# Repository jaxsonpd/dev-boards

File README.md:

# dev-boards
A collection of development boards developed by me

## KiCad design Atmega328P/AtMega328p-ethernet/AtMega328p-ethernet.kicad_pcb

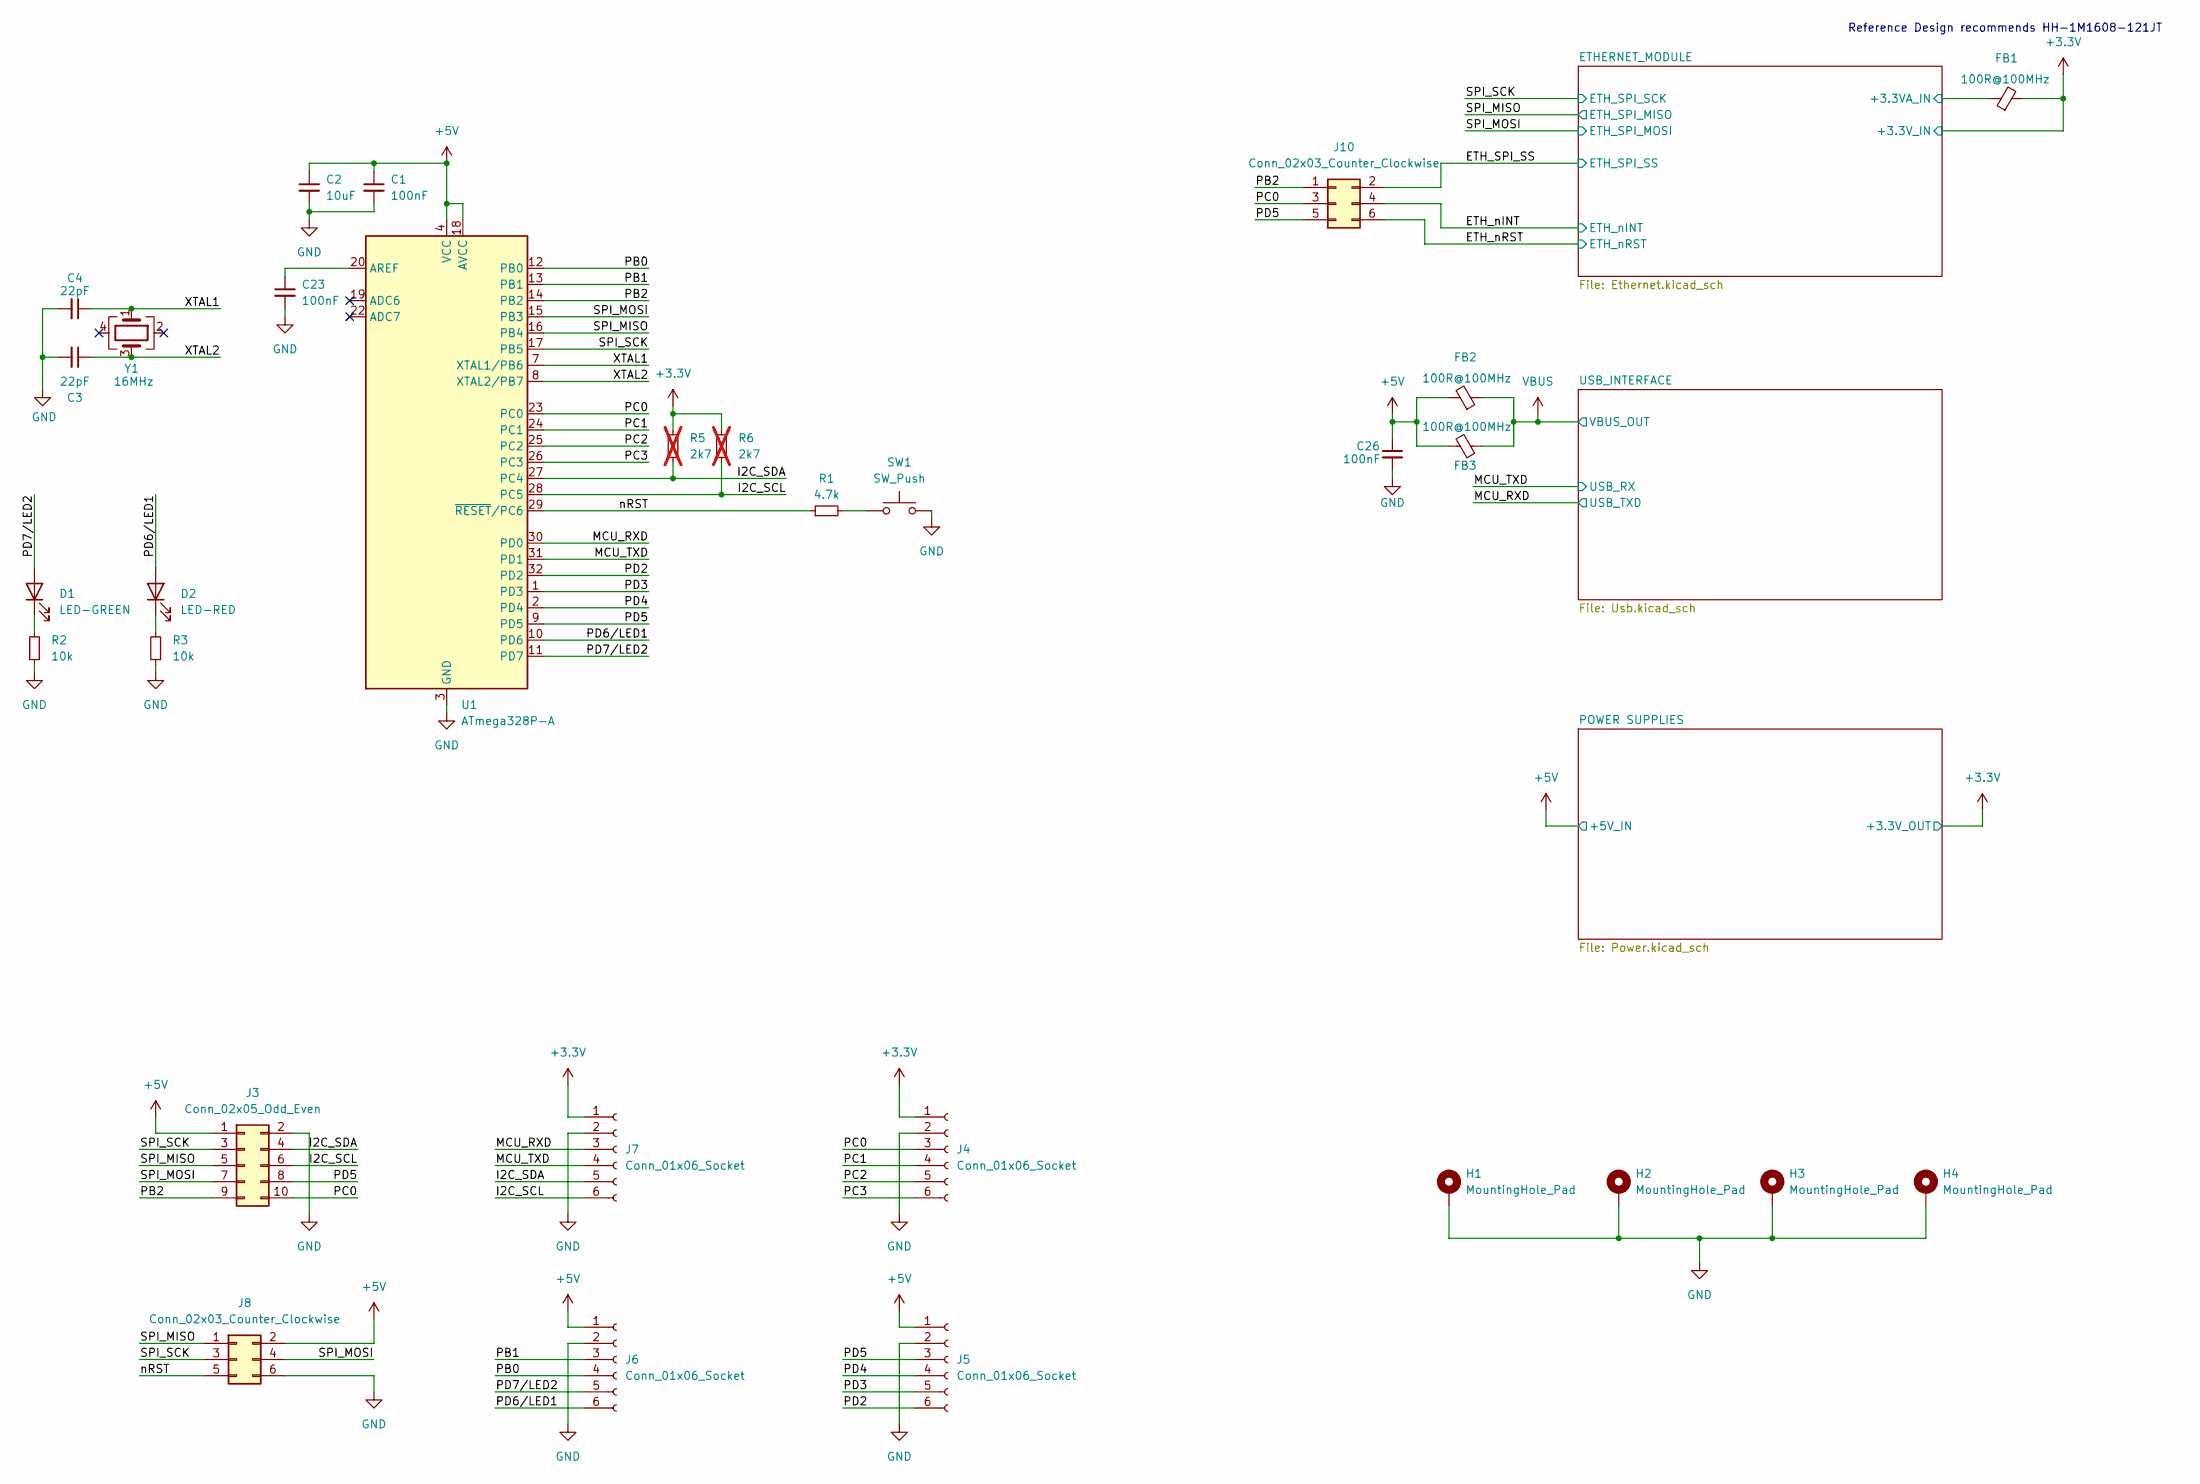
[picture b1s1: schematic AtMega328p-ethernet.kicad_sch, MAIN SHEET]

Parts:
C1, C23, C26: 100nF; C_0603_1608Metric; LCSC C14663
C2: 10uF; C_1206_3216Metric; LCSC C13585
C3, C4: 22pF; C_0603_1608Metric; LCSC C1653
D1: LED-GREEN; LED_0805_2012Metric; LCSC C2297
D2: LED-RED; LED_0805_2012Metric; LCSC C2296
FB1, FB2, FB3: 100R@100MHz; L_0603_1608Metric; LCSC C1015
H1, H2, H3, H4: MountingHole_Pad; MountingHole_3.2mm_M3_DIN965_Pad
J3: Conn_02x05_Odd_Even; IDC-Header_2x05_P2.54mm_Horizontal
J4, J5, J6, J7: Conn_01x06_Socket; PinHeader_1x06_P2.54mm_Vertical
J8, J10: Conn_02x03_Counter_Clockwise; PinHeader_2x03_P2.54mm_Vertical
R1: 4.7k; R_0603_1608Metric; LCSC C23162
R2, R3: 10k; R_0603_1608Metric; LCSC C25804
R5: 2k7; R_0603_1608Metric; LCSC C13167; not fitted
R6: 2k7; R_0603_1608Metric; not fitted
SW1: SW_Push; SW_Push_1P1T_XKB_TS-1187A; LCSC C318884
U1: ATmega328P-A; TQFP-32_7x7mm_P0.8mm; LCSC C14877
Y1: 16MHz; Crystal_SMD_3225-4Pin_3.2x2.5mm; LCSC C13738

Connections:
+3.3V: FB1.2, J4.1, J7.1, R5.2, R6.2; also elsewhere on the board
+5V: C1.1, C2.1, C26.1, FB2.2, FB3.2, J3.1, J5.1, J6.1, J8.2, U1.4 (VCC), U1.6 (VCC), U1.18 (AVCC); also elsewhere on the board
/ETHERNET_MODULE/+3.3VA_IN: FB1.1; also elsewhere on the board
/ETH_SPI_SS: J10.2; also elsewhere on the board
/ETH_nINT: J10.4; also elsewhere on the board
/ETH_nRST: J10.6; also elsewhere on the board
/I2C_SCL: J3.6, J7.6, R6.1, U1.28 (PC5)
/I2C_SDA: J3.4, J7.5, R5.1, U1.27 (PC4)
/MCU_RXD: J7.3, U1.30 (PD0); also elsewhere on the board
/MCU_TXD: J7.4, U1.31 (PD1); also elsewhere on the board
/PB0: J6.4, U1.12 (PB0)
/PB1: J6.3, U1.13 (PB1)
/PB2: J3.9, J10.1, U1.14 (PB2)
/PC0: J3.10, J4.3, J10.3, U1.23 (PC0)
/PC1: J4.4, U1.24 (PC1)
/PC2: J4.5, U1.25 (PC2)
/PC3: J4.6, U1.26 (PC3)
/PD2: J5.6, U1.32 (PD2)
/PD3: J5.5, U1.1 (PD3)
/PD4: J5.4, U1.2 (PD4)
/PD5: J3.8, J5.3, J10.5, U1.9 (PD5)
/PD6/LED1: D2.2 (A), J6.6, U1.10 (PD6)
/PD7/LED2: D1.2 (A), J6.5, U1.11 (PD7)
/SPI_MISO: J3.5, J8.1, U1.16 (PB4); also elsewhere on the board
/SPI_MOSI: J3.7, J8.4, U1.15 (PB3); also elsewhere on the board
/SPI_SCK: J3.3, J8.3, U1.17 (PB5); also elsewhere on the board
/XTAL1: C4.1, U1.7 (XTAL1/PB6), Y1.1
/XTAL2: C3.1, U1.8 (XTAL2/PB7), Y1.3
/nRST: J8.5, R1.1, U1.29 (~RESET/PC6)
GND: C1.2, C2.2, C3.2, C4.2, C23.2, C26.2, H1.1, H2.1, H3.1, H4.1, J3.2, J4.2, J5.2, J6.2, J7.2, J8.6, R2.1, R3.1, SW1.2, U1.3 (GND), U1.5 (GND), U1.21 (GND); also elsewhere on the board
unnamed: D1.1 (K), R2.2
unnamed: D2.1 (K), R3.2
unnamed: R1.2, SW1.1
unnamed: C23.1, U1.20 (AREF)
VBUS: FB2.1, FB3.1; also elsewhere on the board

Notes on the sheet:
Reference Design recommends HH-1M1608-121JT

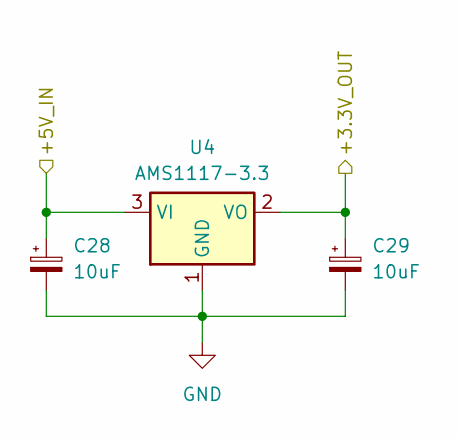
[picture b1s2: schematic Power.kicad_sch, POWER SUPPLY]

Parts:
C28, C29: 10uF; C_1206_3216Metric; LCSC C13585
U4: AMS1117-3.3; SOT-223-3_TabPin2; LCSC C6186

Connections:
+3.3V: C29.1, U4.2 (VO); also elsewhere on the board
+5V: C28.1, U4.3 (VI); also elsewhere on the board
GND: C28.2, C29.2, U4.1 (GND); also elsewhere on the board

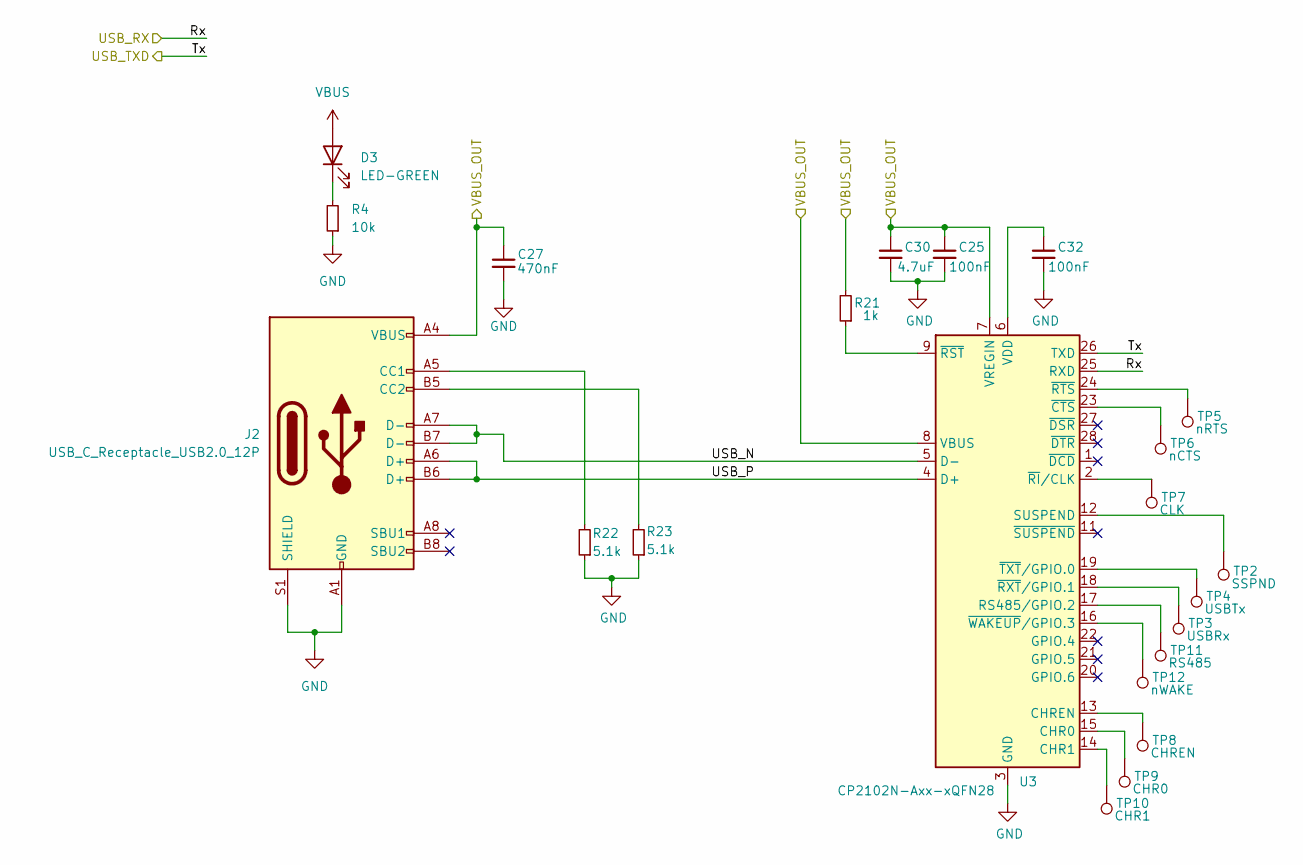
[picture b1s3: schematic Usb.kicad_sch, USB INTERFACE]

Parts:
C25, C32: 100nF; C_0603_1608Metric; LCSC C1647
C27: 470nF; C_0603_1608Metric; LCSC C1623
C30: 4.7uF; C_0603_1608Metric; LCSC C1647
D3: LED-GREEN; LED_0805_2012Metric; LCSC C2297
J2: USB_C_Receptacle_USB2.0_12P; USB_C_Receptacle_G-Switch_GT-USB-7010ASV; LCSC C2988369
R4: 10k; R_0603_1608Metric; LCSC C25804
R21: 1k; R_0603_1608Metric; LCSC C21190
R22, R23: 5.1k; R_0603_1608Metric; LCSC C23186
TP2: SSPND; TestPoint_Pad_1.0x1.0mm
TP3: USBRx; TestPoint_Pad_1.0x1.0mm
TP4: USBTx; TestPoint_Pad_1.0x1.0mm
TP5: nRTS; TestPoint_Pad_1.0x1.0mm
TP6: nCTS; TestPoint_Pad_1.0x1.0mm
TP7: CLK; TestPoint_Pad_1.0x1.0mm
TP8: CHREN; TestPoint_Pad_1.0x1.0mm
TP9: CHR0; TestPoint_Pad_1.0x1.0mm
TP10: CHR1; TestPoint_Pad_1.0x1.0mm
TP11: RS485; TestPoint_Pad_1.0x1.0mm
TP12: nWAKE; TestPoint_Pad_1.0x1.0mm
U3: CP2102N-Axx-xQFN28; QFN-28-1EP_5x5mm_P0.5mm_EP3.35x3.35mm; LCSC C6568

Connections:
/MCU_RXD: U3.26 (TXD); also elsewhere on the board
/MCU_TXD: U3.25 (RXD); also elsewhere on the board
/USB_INTERFACE/USB_N: J2.A7 (D-), J2.B7 (D-), U3.5 (D-)
/USB_INTERFACE/USB_P: J2.A6 (D+), J2.B6 (D+), U3.4 (D+)
GND: C25.2, C27.2, C30.2, C32.2, J2.A1 (GND), J2.A12 (GND), J2.B1 (GND), J2.B12 (GND), J2.S1 (SHIELD), R4.1, R22.1, R23.1, U3.3 (GND), U3.29 (GND); also elsewhere on the board
unnamed: D3.1 (K), R4.2
unnamed: J2.A5 (CC1), R22.2
unnamed: J2.B5 (CC2), R23.2
unnamed: TP9.1, U3.15 (CHR0)
unnamed: TP10.1, U3.14 (CHR1)
unnamed: TP8.1, U3.13 (CHREN)
unnamed: TP11.1, U3.17 (RS485/GPIO.2)
unnamed: TP2.1, U3.12 (SUSPEND)
unnamed: C32.1, U3.6 (VDD)
unnamed: TP6.1, U3.23 (~CTS)
unnamed: TP7.1, U3.2 (~RI/CLK)
unnamed: R21.1, U3.9 (~RST)
unnamed: TP5.1, U3.24 (~RTS)
unnamed: TP3.1, U3.18 (~RXT/GPIO.1)
unnamed: TP4.1, U3.19 (~TXT/GPIO.0)
unnamed: TP12.1, U3.16 (~WAKEUP/GPIO.3)
VBUS: C25.1, C27.1, C30.1, D3.2 (A), J2.A4 (VBUS), J2.A9 (VBUS), J2.B4 (VBUS), J2.B9 (VBUS), R21.2, U3.7 (VREGIN), U3.8 (VBUS); also elsewhere on the board

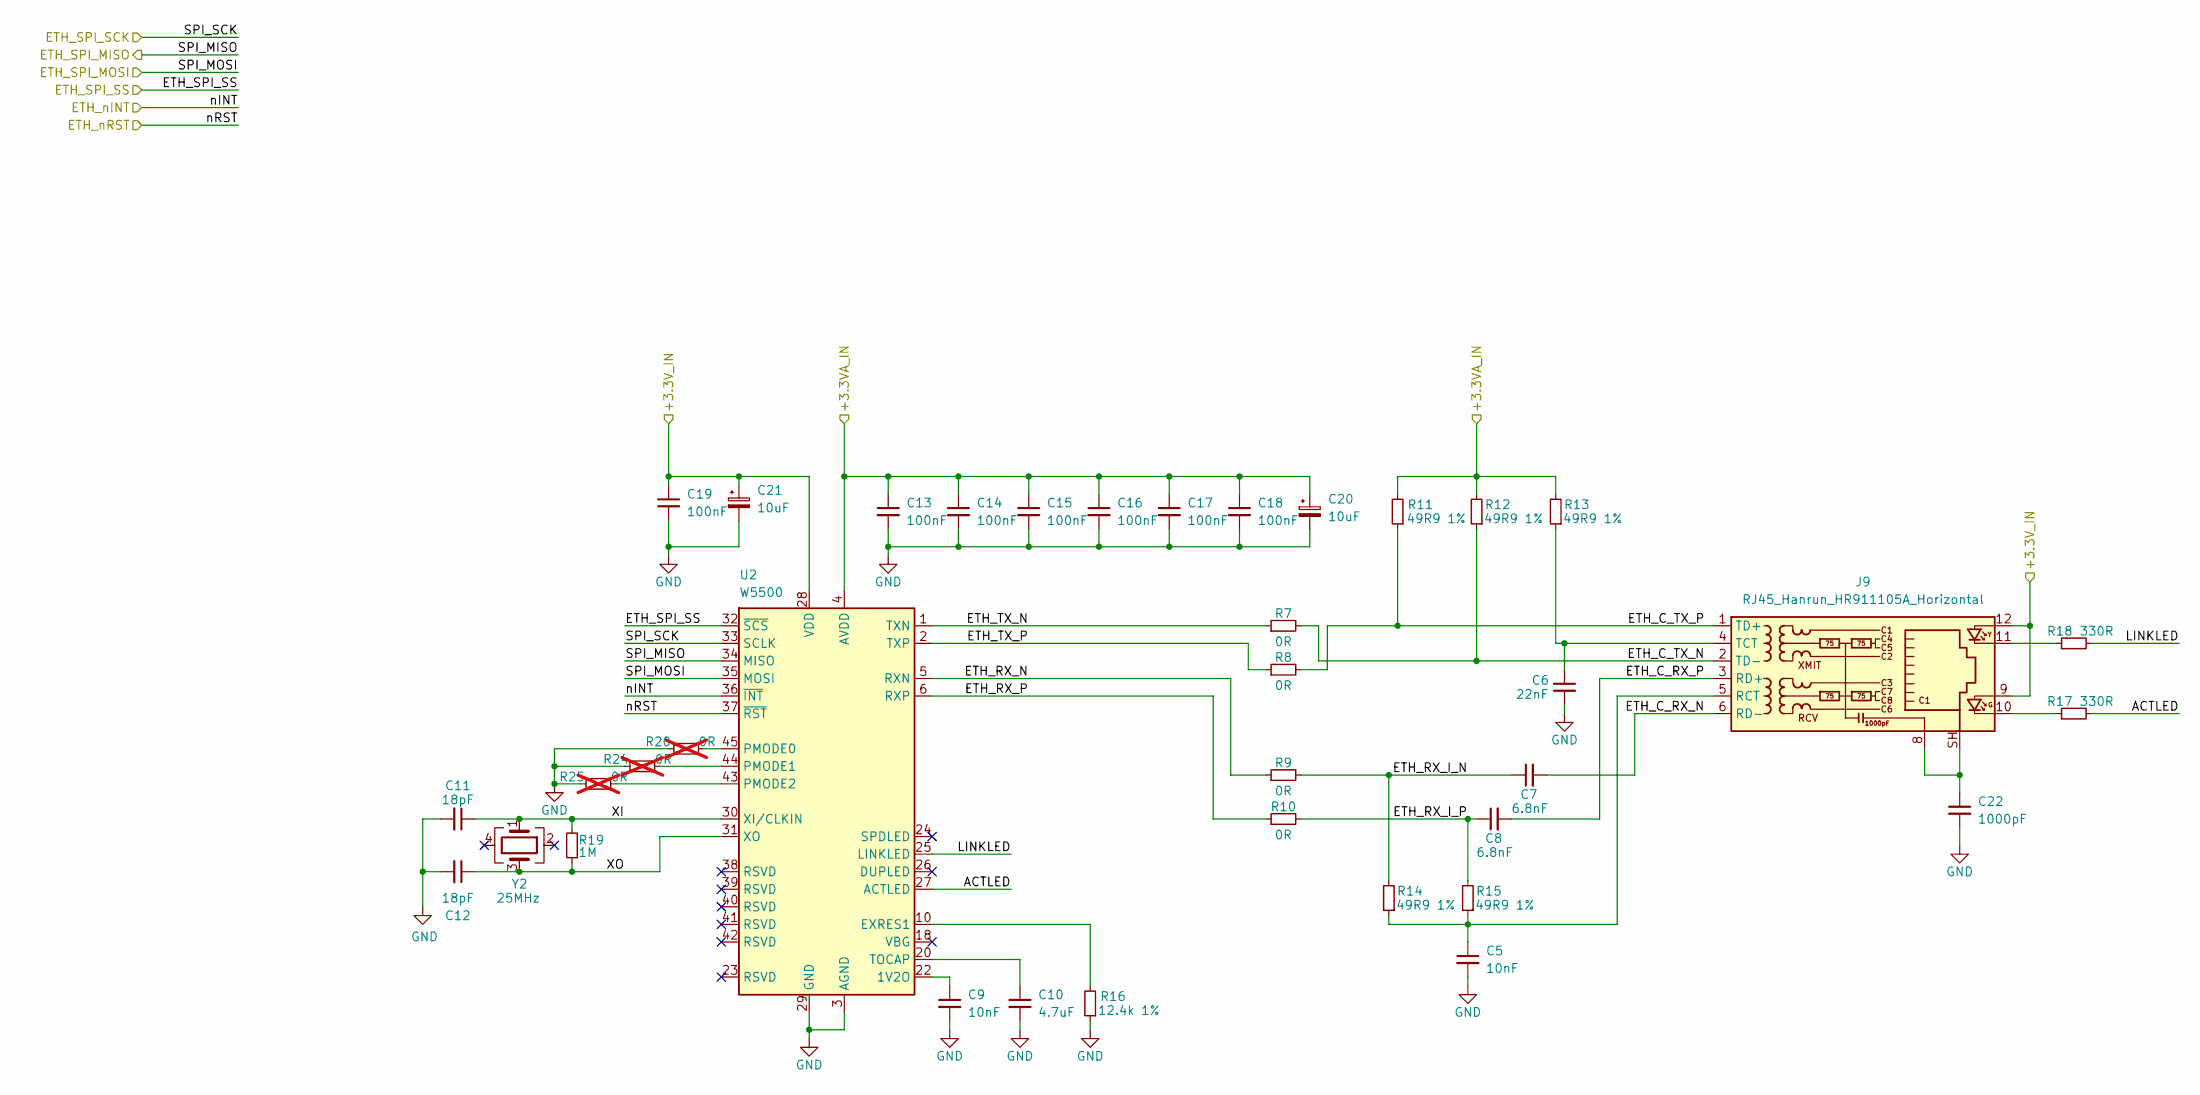
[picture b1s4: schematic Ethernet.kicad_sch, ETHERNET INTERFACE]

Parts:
C5, C9: 10nF; C_0603_1608Metric; LCSC C57112
C6: 22nF; C_0603_1608Metric; LCSC C21122
C7, C8: 6.8nF; C_0603_1608Metric; LCSC C1631
C10: 4.7uF; C_0805_2012Metric; LCSC C1779
C11, C12: 18pF; C_0603_1608Metric; LCSC C1647
C13, C14, C15, C16, C17, C18, C19: 100nF; C_0603_1608Metric; LCSC C14663
C20, C21: 10uF; C_1206_3216Metric; LCSC C13585
C22: 1000pF; C_0603_1608Metric; LCSC C57112
J9: RJ45_Hanrun_HR911105A_Horizontal; LCSC C12074
R7: 0R; R_0805_2012Metric_Pad1.20x1.40mm_HandSolder; LCSC C21189
R8, R9, R10: 0R; R_0805_2012Metric_Pad1.20x1.40mm_HandSolder
R11: 49R9 1%; R_0603_1608Metric; LCSC C23185
R12, R13, R14, R15: 49R9 1%; R_0603_1608Metric
R16: 12.4k 1%; R_0805_2012Metric_Pad1.20x1.40mm_HandSolder
R17: 330R; R_0603_1608Metric; LCSC C23138
R18: 330R; R_0603_1608Metric
R19: 1M; R_0603_1608Metric; LCSC C22935
R20, R24, R25: 0R; R_0805_2012Metric_Pad1.20x1.40mm_HandSolder; not fitted
U2: W5500; LQFP-48_7x7mm_P0.5mm; LCSC C32843
Y2: 25MHz; Crystal_SMD_3225-4Pin_3.2x2.5mm; LCSC C9006

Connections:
+3.3V: C19.1, C21.1, J9.9, J9.12, U2.28 (VDD); also elsewhere on the board
/ETHERNET_MODULE/+3.3VA_IN: C13.1, C14.1, C15.1, C16.1, C17.1, C18.1, C20.1, R11.2, R12.2, R13.2, U2.4 (AVDD), U2.8 (AVDD), U2.11 (AVDD), U2.15 (AVDD), U2.17 (AVDD), U2.21 (AVDD); also elsewhere on the board
/ETHERNET_MODULE/ACTLED: R17.2, U2.27 (ACTLED)
/ETHERNET_MODULE/ETH_C_RX_N: C7.2, J9.6 (RD-)
/ETHERNET_MODULE/ETH_C_RX_P: C8.2, J9.3 (RD+)
/ETHERNET_MODULE/ETH_C_TX_N: J9.2 (TD-), R7.2, R12.1
/ETHERNET_MODULE/ETH_C_TX_P: J9.1 (TD+), R8.2, R11.1
/ETHERNET_MODULE/ETH_RX_I_N: C7.1, R9.2, R14.2
/ETHERNET_MODULE/ETH_RX_I_P: C8.1, R10.2, R15.2
/ETHERNET_MODULE/ETH_RX_N: R9.1, U2.5 (RXN)
/ETHERNET_MODULE/ETH_RX_P: R10.1, U2.6 (RXP)
/ETHERNET_MODULE/ETH_TX_N: R7.1, U2.1 (TXN)
/ETHERNET_MODULE/ETH_TX_P: R8.1, U2.2 (TXP)
/ETHERNET_MODULE/LINKLED: R18.2, U2.25 (LINKLED)
/ETHERNET_MODULE/XI: C11.1, R19.2, U2.30 (XI/CLKIN), Y2.1
/ETHERNET_MODULE/XO: C12.1, R19.1, U2.31 (XO), Y2.3
/ETH_SPI_SS: U2.32 (~SCS); also elsewhere on the board
/ETH_nINT: U2.36 (~INT); also elsewhere on the board
/ETH_nRST: U2.37 (~RST); also elsewhere on the board
/SPI_MISO: U2.34 (MISO); also elsewhere on the board
/SPI_MOSI: U2.35 (MOSI); also elsewhere on the board
/SPI_SCK: U2.33 (SCLK); also elsewhere on the board
GND: C5.2, C6.2, C9.2, C10.2, C11.2, C12.2, C13.2, C14.2, C15.2, C16.2, C17.2, C18.2, C19.2, C20.2, C21.2, C22.2, R16.1, R20.1, R24.1, R25.1, U2.3 (AGND), U2.9 (AGND), U2.14 (AGND), U2.16 (AGND), U2.19 (AGND), U2.29 (GND), U2.48 (AGND); also elsewhere on the board
unnamed: C22.1, J9.8, J9.SH
unnamed: J9.10, R17.1
unnamed: J9.11, R18.1
unnamed: C5.1, J9.5 (RCT), R14.1, R15.1
unnamed: C6.1, J9.4 (TCT), R13.1
unnamed: C9.1, U2.22 (1V2O)
unnamed: R16.2, U2.10 (EXRES1)
unnamed: R20.2, U2.45 (PMODE0)
unnamed: R24.2, U2.44 (PMODE1)
unnamed: R25.2, U2.43 (PMODE2)
unnamed: C10.1, U2.20 (TOCAP)

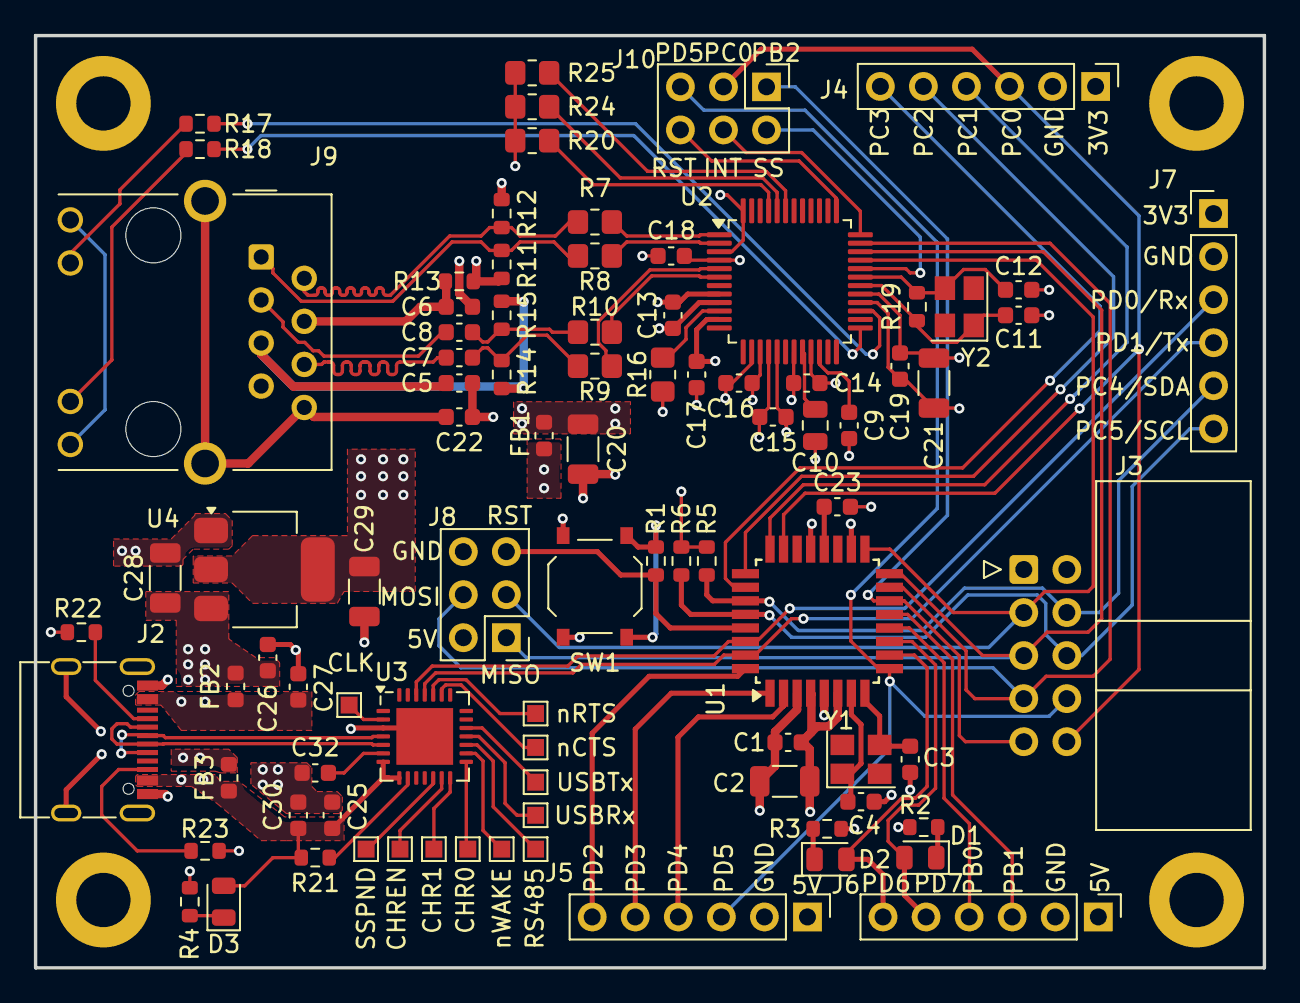
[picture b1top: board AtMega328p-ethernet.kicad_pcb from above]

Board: 4 copper layers, 72.5 x 55.0 mm, 92 parts (0 on the bottom side), 78 nets.

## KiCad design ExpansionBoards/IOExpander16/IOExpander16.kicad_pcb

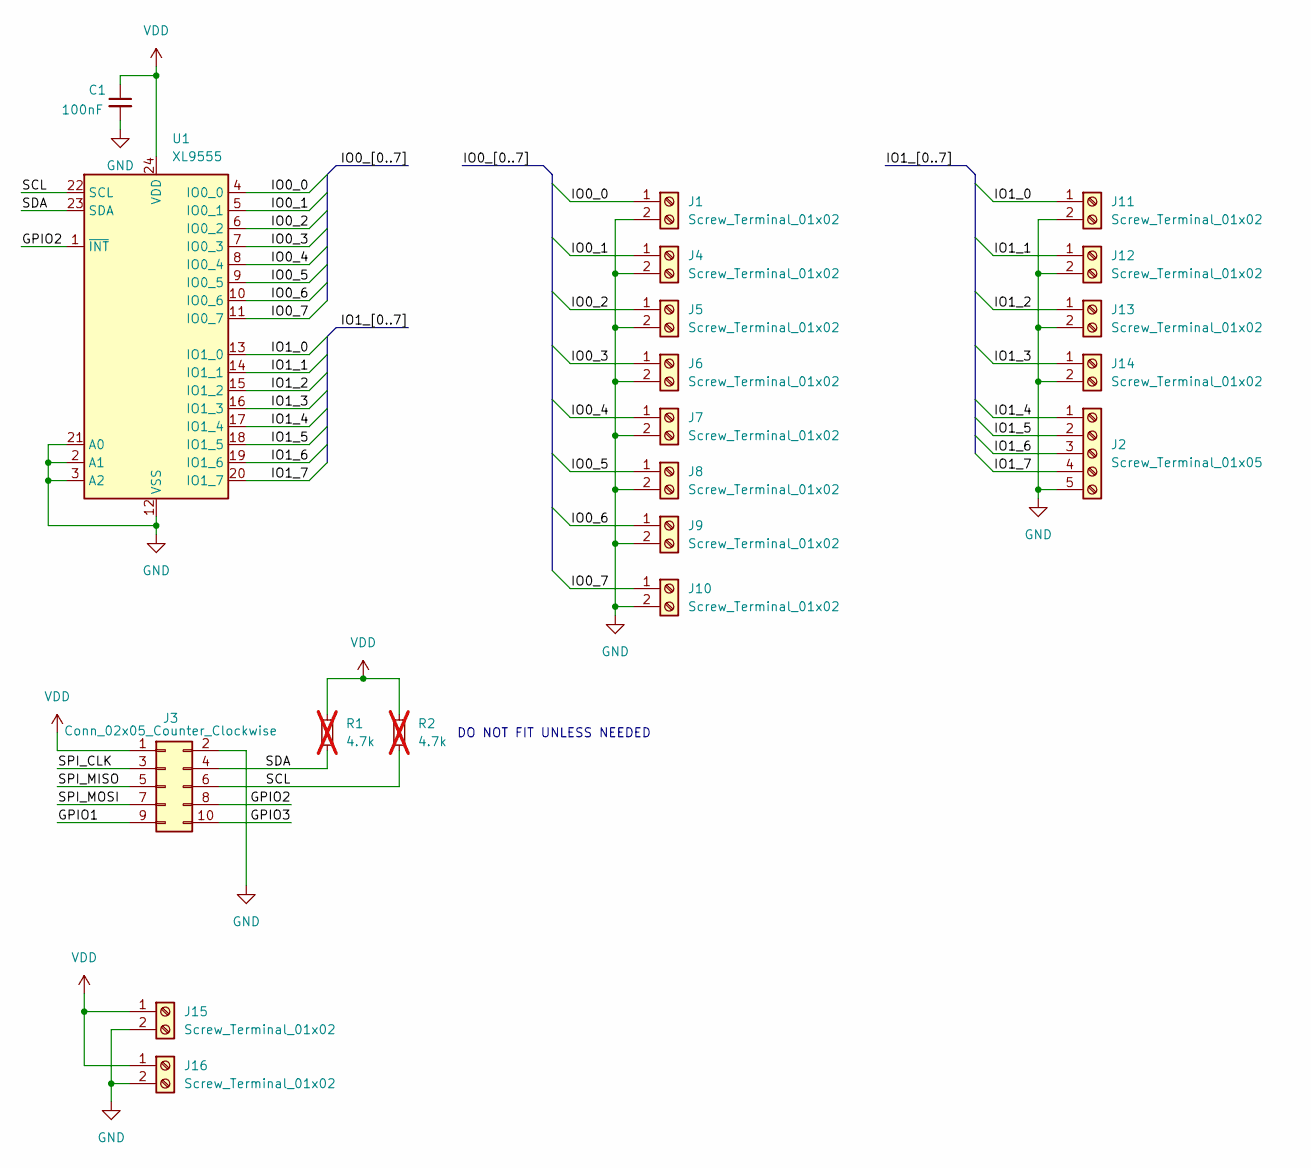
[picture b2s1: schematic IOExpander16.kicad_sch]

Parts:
C1: 100nF; C_Disc_D3.0mm_W1.6mm_P2.50mm
J1, J4, J5, J6, J7, J8, J9, J10, J11, J12, J13, J14, J15, J16: Screw_Terminal_01x02; WJ15EDGRC-3.81-2P
J2: Screw_Terminal_01x05; WJ15EDGRC-3.81-5P
J3: Conn_02x05_Counter_Clockwise; IDC-Header_2x05_P2.54mm_Horizontal
R1, R2: 4.7k; R_Axial_DIN0411_L9.9mm_D3.6mm_P12.70mm_Horizontal; not fitted
U1: XL9555; TSSOP-24_4.4x7.8mm_P0.65mm

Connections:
/GPIO1: J3.9
/GPIO2: J3.8, U1.1 (~INT)
/GPIO3: J3.10
/IO0_0: J1.1, U1.4 (IO0_0)
/IO0_1: J4.1, U1.5 (IO0_1)
/IO0_2: J5.1, U1.6 (IO0_2)
/IO0_3: J6.1, U1.7 (IO0_3)
/IO0_4: J7.1, U1.8 (IO0_4)
/IO0_5: J8.1, U1.9 (IO0_5)
/IO0_6: J9.1, U1.10 (IO0_6)
/IO0_7: J10.1, U1.11 (IO0_7)
/IO1_0: J11.1, U1.13 (IO1_0)
/IO1_1: J12.1, U1.14 (IO1_1)
/IO1_2: J13.1, U1.15 (IO1_2)
/IO1_3: J14.1, U1.16 (IO1_3)
/IO1_4: J2.1, U1.17 (IO1_4)
/IO1_5: J2.2, U1.18 (IO1_5)
/IO1_6: J2.3, U1.19 (IO1_6)
/IO1_7: J2.4, U1.20 (IO1_7)
/SCL: J3.6, R2.2, U1.22 (SCL)
/SDA: J3.4, R1.2, U1.23 (SDA)
/SPI_CLK: J3.3
/SPI_MISO: J3.5
/SPI_MOSI: J3.7
GND: C1.2, J1.2, J2.5, J3.2, J4.2, J5.2, J6.2, J7.2, J8.2, J9.2, J10.2, J11.2, J12.2, J13.2, J14.2, J15.2, J16.2, U1.2 (A1), U1.3 (A2), U1.12 (VSS), U1.21 (A0)
VDD: C1.1, J3.1, J15.1, J16.1, R1.1, R2.1, U1.24 (VDD)

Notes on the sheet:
DO NOT FIT UNLESS NEEDED

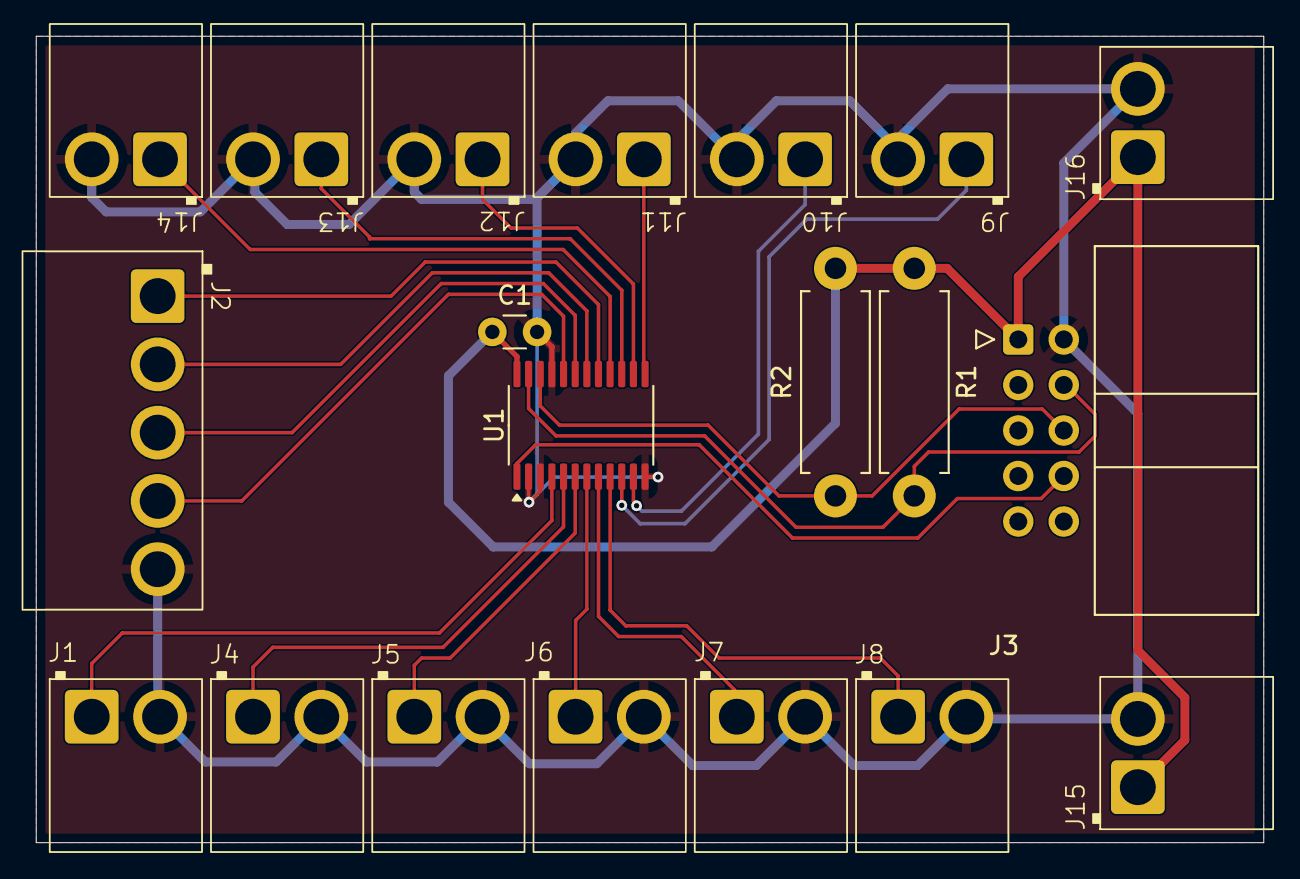
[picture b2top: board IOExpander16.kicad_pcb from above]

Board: 2 copper layers, 68.5 x 45.0 mm, 20 parts (0 on the bottom side), 21 nets.

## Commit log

2025-02-19 Initial Component Selection Started
2025-02-20 continued work on sechematic
2025-02-21 Continued work on ethernet
2025-02-21 Most main components layed out
2025-02-21 Schematic draft complete
2025-02-21 PCB Layout done initial
2025-02-25 Added dif pair and finished USB schematic
2025-02-25 Added lots of lcsc part numbers
2025-02-27 Most components selected using lcsc
2025-02-27 All parts matching lcsc replaced usb transever
2025-02-28 Continued cleanup
2025-02-28 USB and microcontroller layed out
2025-03-04 IO expander initial layout complete
2025-03-04 Most components layed out and locked still to do ethernet
2025-03-12 Layout complete ready for review
2025-03-13 Most traces complete just GPIO left
2025-03-14 Tracing complete ready for final check and silk screen.
2025-03-15 IO expansion board layout compeleted ready for review.
2025-03-17 Ethernet atmega328p reviewed
2025-03-17 Expansion board review complete
2025-04-28 Added pin descriptions
2025-04-28 Completed board component rotation adjustments
